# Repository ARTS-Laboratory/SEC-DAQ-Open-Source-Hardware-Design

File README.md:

# SEC DAQ
A 4-channel, 100 pF capacitance DAQ with active shielding designed for use with the Soft Elastomeric Capacitor (SEC) sensors but could be used for anything. 

This data acquisition can measure SECs in the range of 15-115 pF, with an asynchronous sampling speed of 400 S/s on a single channel.

This hardware was used in various papers, including:
1. Downey, Austin, Anna Laura Pisello, Elena Fortunati, Claudia Fabiani, Francesca Luzi, Luigi Torre, Filippo Ubertini, and Simon Laflamme. "Durability and weatherability of a styrene-ethylene-butylene-styrene (SEBS) block copolymer-based sensing skin for civil infrastructure applications." Sensors and Actuators A: Physical 293 (2019): 269-280.
1. Downey, Austin, Mohammadkazem Sadoughi, Simon Laflamme, and Chao Hu. "Fusion of sensor geometry into additive strain fields measured with sensing skin." Smart Materials and Structures 27, no. 7 (2018): 075033.
1. Yan, Jin, Austin Downey, Alessandro Cancelli, Simon Laflamme, An Chen, Jian Li, and Filippo Ubertini. "Concrete crack detection and monitoring using a capacitive dense sensor array." Sensors 19, no. 8 (2019): 1843.

## Hardware design notes

### v0.9.0
1. Contains all the older files. 
1. Contains the 2-board PCB design

### v0.9.1
1. This is stable release. 
1. A 4-channel SEC DAC with isolated signal

### v0.9.2 (future version)
Improvements needed

#### High importance
1. The files needs to be cleaned up, and put back into a single KiCad file.
1. Compress the board layout so the DAQ sits inside the Arduino shield. (Reduces the wasted space)
1. Remove the ground tabs as adding a shield is a further work outside of these single box DAQs
1. Use a lower current draw opotcoupler, I think a CPC1301 should work. 
 
#### Medium importance
1. Move trigger housing into the board so it does not hang over.
1. Change the surface mount D-sub to a edge mount D-sub with signal/shield on top and ground on bottom. 
1. Add a switch for the time stamp so the DAQ only returns a time stamp if the switch in enabled. Will require a 14 pin IDC connector.

#### Low importance 
1. Enlarge the CDC filter capacitor solder pads
1. Add LED to the trigger circuit to help with trouble shooting (check current draw problems)

## Licensing and Citation

[![CC BY-SA 4.0][cc-by-sa-shield]][cc-by-sa]

This work is licensed under a
[Creative Commons Attribution-ShareAlike 4.0 International License][cc-by-sa].

[cc-by-sa]: http://creativecommons.org/licenses/by-sa/4.0/
[cc-by-sa-image]: https://licensebuttons.net/l/by-sa/4.0/88x31.png
[cc-by-sa-shield]: https://img.shields.io/badge/License-CC%20BY--SA%204.0-lightgrey.svg

Cite as:

@Misc{DowneySECDAQ,   
  author       = {Austin Downey},   
  howpublished = {GitHub},  
  title        = {{SEC} {DAQ} Open Source Hardware Design},   
  groups       = {{ARTS-L}ab},  
  url          = {https://github.com/ARTS-Laboratory/SEC-DAQ-Open-Source-Hardware-Design},  
}

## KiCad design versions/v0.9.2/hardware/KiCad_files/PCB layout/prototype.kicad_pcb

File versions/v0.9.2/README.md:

# V0.9.2

## Hardware
PCB EDA files.

## Software
Arudino and LabVIEW source code.

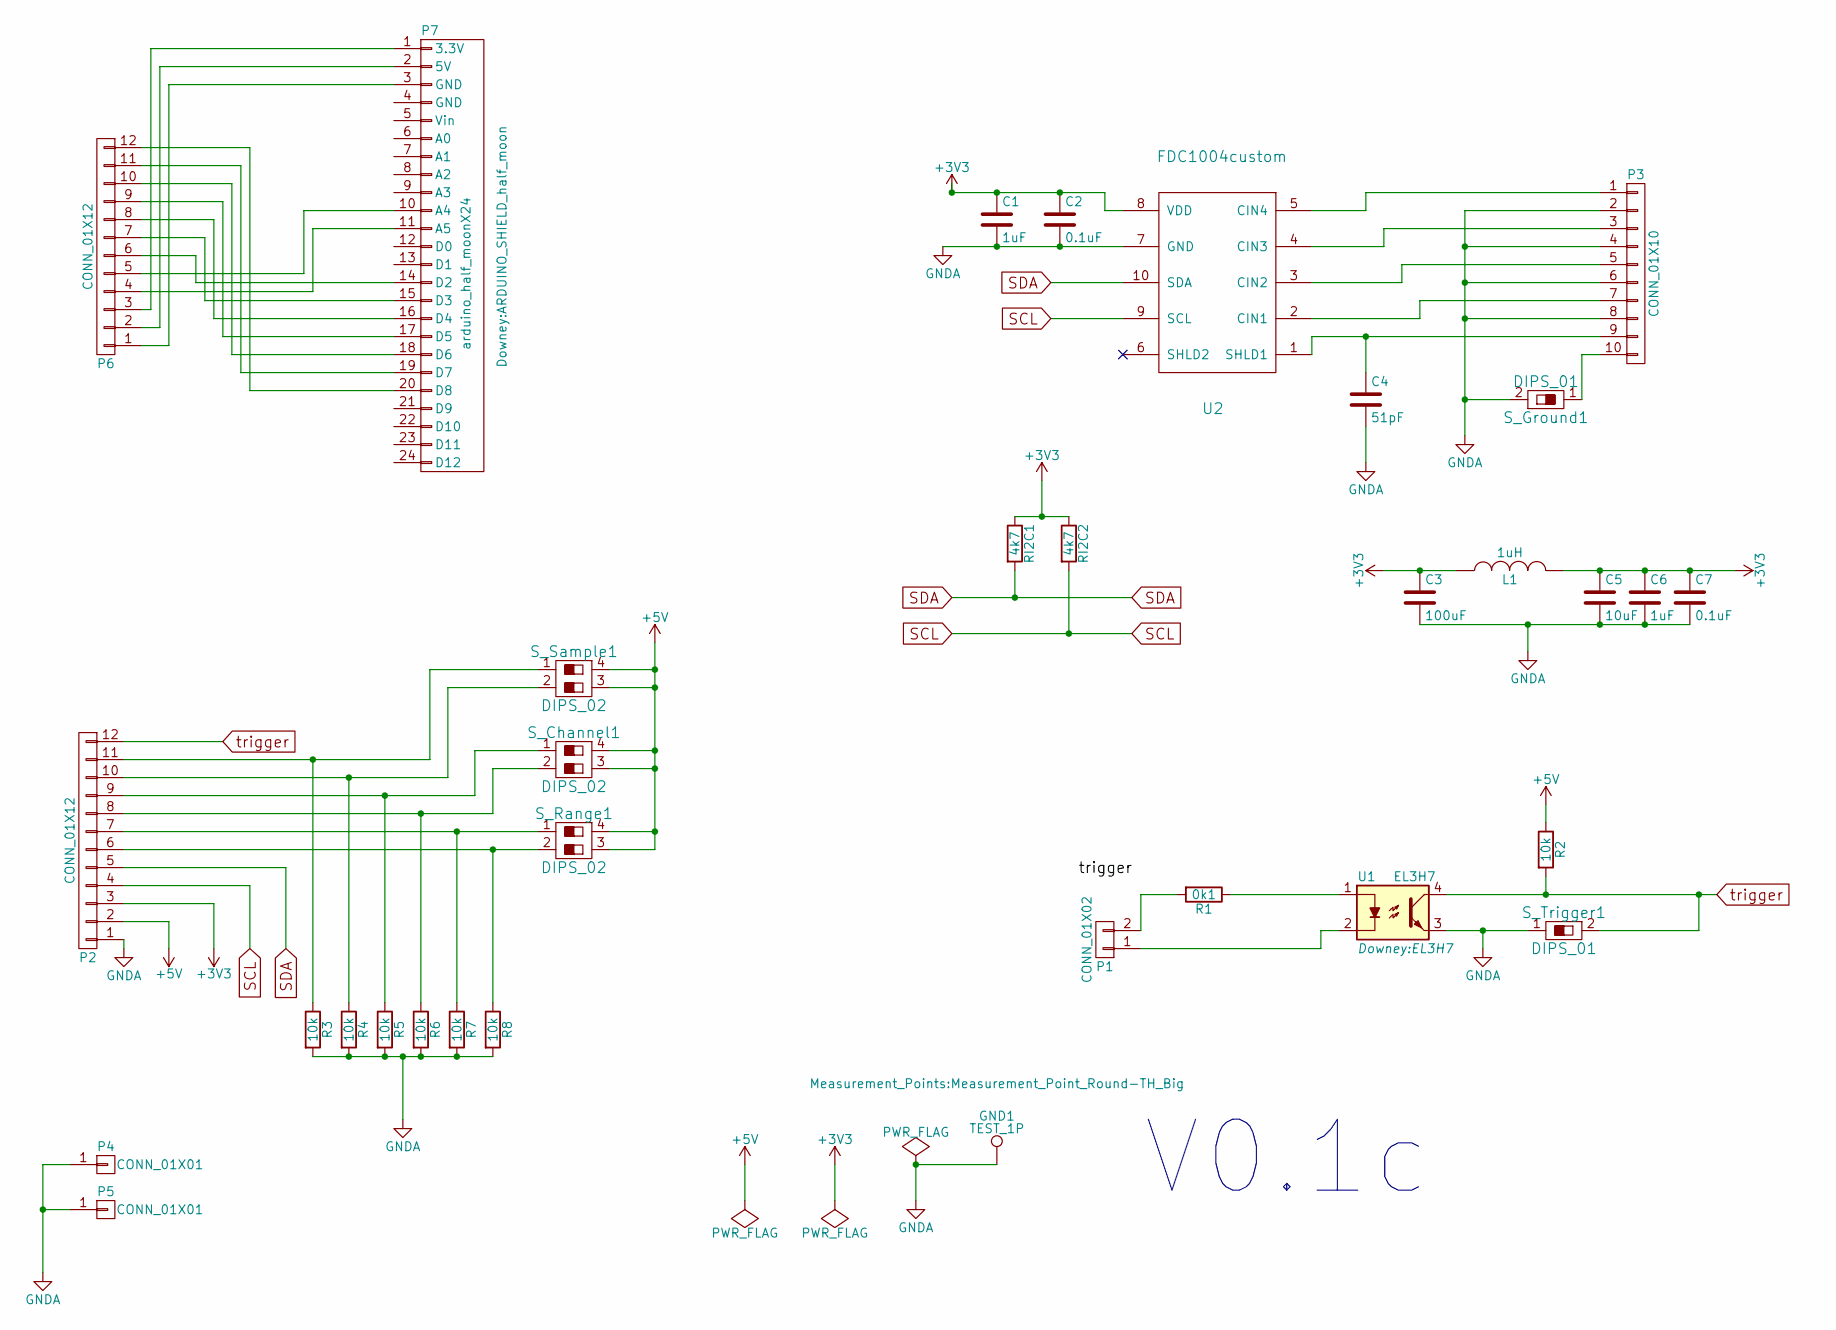
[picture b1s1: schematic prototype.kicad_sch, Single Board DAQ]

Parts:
C1, C6: 1uF; C_0805_HandSoldering
C2, C7: 0.1uF; C_0805_HandSoldering
C3: 100uF; C_1206_HandSoldering
C4: 51pF; C_0805_HandSoldering
C5: 10uF; C_0805_HandSoldering
GND1: TEST_1P; Measurement_Point_Round-TH_Big
L1: 1uH; R_0805_HandSoldering
P1: CONN_01X02; Pin_Header_Straight_1x02_Pitch2.00mm
P2, P6: CONN_01X12; 3M_12POS_ribbon_conn
P3: CONN_01X10; DSUB-9_surface_mount
P4, P5: CONN_01X01; 1Pin
P7: arduino_half_moonX24; ARDUINO_SHIELD_half_moon
R1: 0k1; R_1206_HandSoldering
R2, R3, R4, R5, R6, R7, R8: 10k; R_1206_HandSoldering
RI2C1, RI2C2: 4k7; R_1206_HandSoldering
S_Channel1: DIPS_02; SW_DIP_x2_W7.62mm_Slide
S_Ground1: DIPS_01; SW_DIP_x1_W7.62mm_Slide
S_Range1: DIPS_02; SW_DIP_x2_W7.62mm_Slide
S_Sample1: DIPS_02; SW_DIP_x2_W7.62mm_Slide
S_Trigger1: DIPS_01; SW_DIP_x1_W7.62mm_Slide
U1: EL3H7
U2: FDC1004custom; SOIC_10_FDC1004

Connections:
+3V3: C1.1, C2.1, C3.1, C5.1, C6.1, C7.1, L1.1, L1.2, P2.3, RI2C1.1, RI2C2.1, U2.8 (VDD)
+5V: P2.2, R2.1, S_Channel1.3, S_Channel1.4, S_Range1.3, S_Range1.4, S_Sample1.3, S_Sample1.4
GNDA: C1.2, C2.2, C3.2, C4.2, C5.2, C6.2, C7.2, GND1.1, P2.1, P3.2, P3.4, P3.6, P3.8, P4.1, P5.1, R3.2, R4.2, R5.2, R6.2, R7.2, R8.2, S_Ground1.2, S_Trigger1.1, U1.3, U2.7 (GND)
unnamed: C4.1, P3.9, U2.1 (SHLD1)
unnamed: P1.1, U1.2
unnamed: P1.2, R1.2
unnamed: P2.6, R8.1, S_Range1.2
unnamed: P2.7, R7.1, S_Range1.1
unnamed: P2.8, R6.1, S_Channel1.2
unnamed: P2.9, R5.1, S_Channel1.1
unnamed: P2.10, R4.1, S_Sample1.2
unnamed: P2.11, R3.1, S_Sample1.1
unnamed: P3.1, U2.5 (CIN4)
unnamed: P3.3, U2.4 (CIN3)
unnamed: P3.5, U2.3 (CIN2)
unnamed: P3.7, U2.2 (CIN1)
unnamed: P3.10, S_Ground1.1
unnamed: P6.1, P7.3 (GND)
unnamed: P6.2, P7.2 (5V)
unnamed: P6.3, P7.1 (3.3V)
unnamed: P6.4, P7.11 (A5)
unnamed: P6.5, P7.10 (A4)
unnamed: P6.6, P7.14 (D2)
unnamed: P6.7, P7.15 (D3)
unnamed: P6.8, P7.16 (D4)
unnamed: P6.9, P7.17 (D5)
unnamed: P6.10, P7.18 (D6)
unnamed: P6.11, P7.19 (D7)
unnamed: P6.12, P7.20 (D8)
unnamed: R1.1, U1.1
SCL: P2.4, RI2C2.2, U2.9 (SCL)
SDA: P2.5, RI2C1.2, U2.10 (SDA)
trigger: P2.12, R2.2, S_Trigger1.2, U1.4

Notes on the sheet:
V0.1c

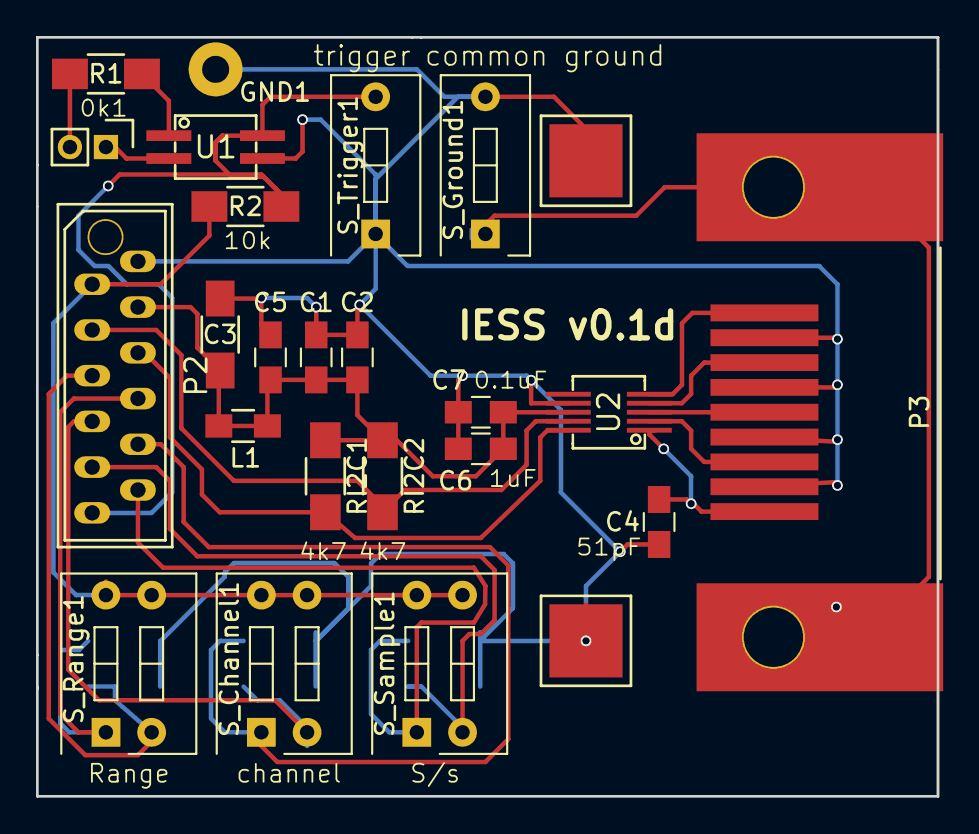
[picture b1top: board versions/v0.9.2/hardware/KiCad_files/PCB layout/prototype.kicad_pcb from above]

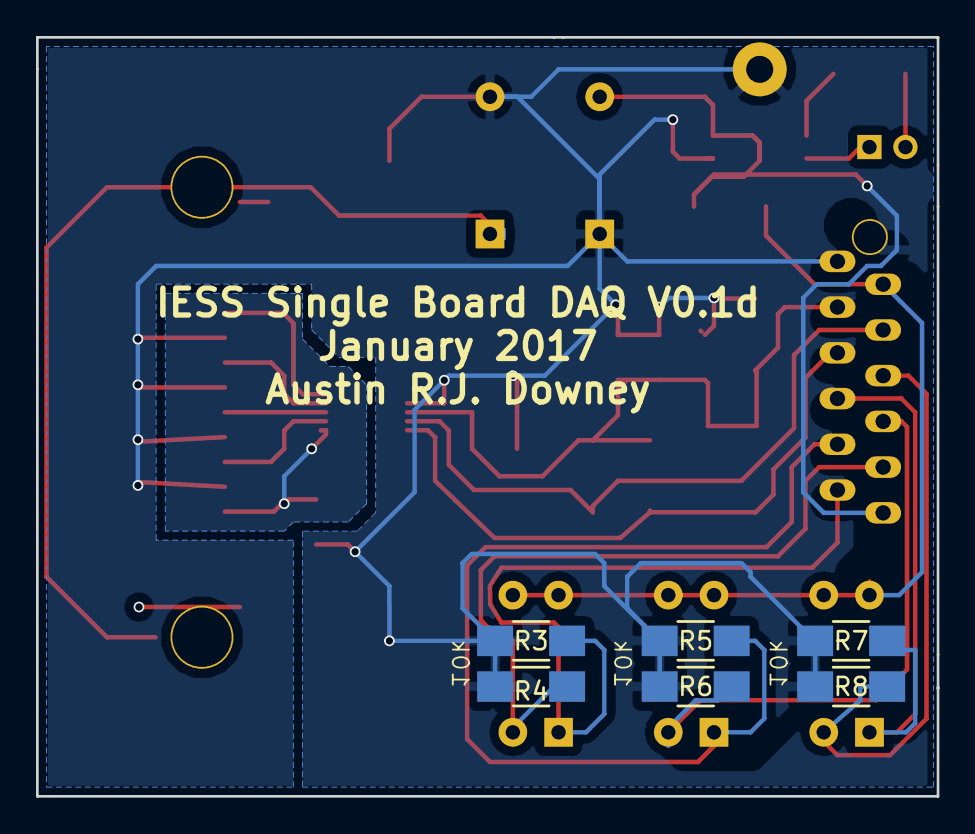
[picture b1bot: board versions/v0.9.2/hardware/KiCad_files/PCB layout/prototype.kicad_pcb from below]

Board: 2 copper layers, 50.0 x 42.2 mm, 31 parts (6 on the bottom side), 21 nets.

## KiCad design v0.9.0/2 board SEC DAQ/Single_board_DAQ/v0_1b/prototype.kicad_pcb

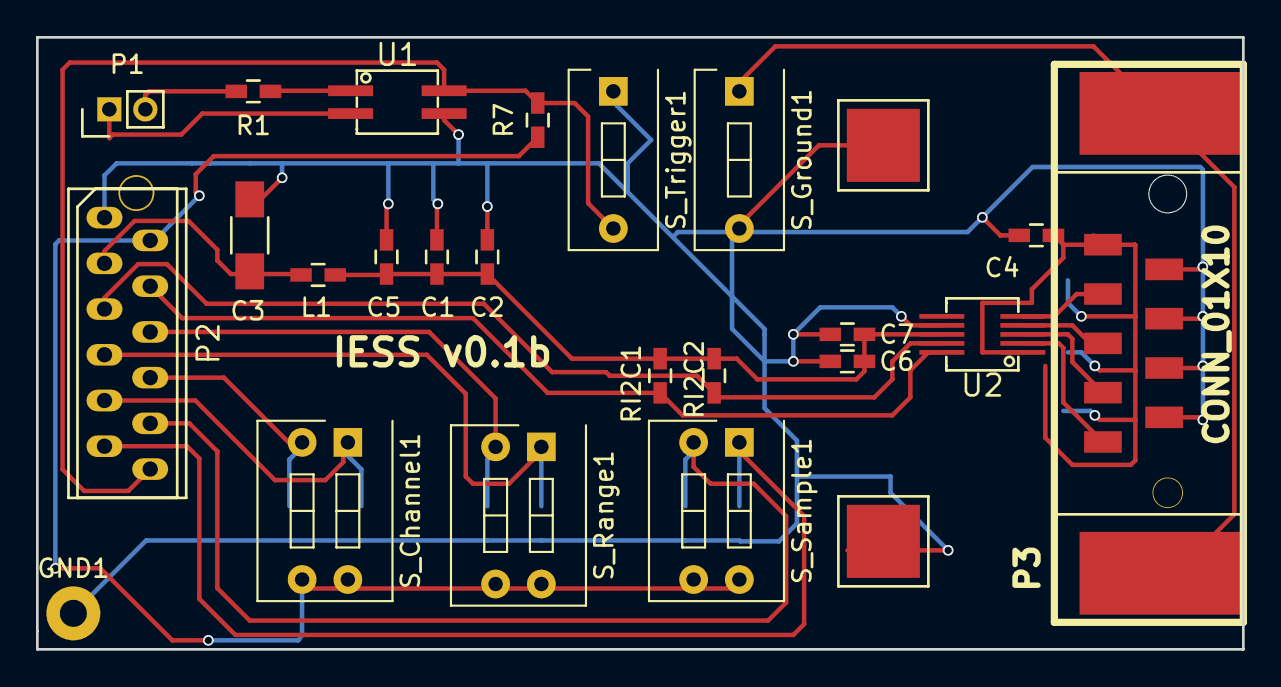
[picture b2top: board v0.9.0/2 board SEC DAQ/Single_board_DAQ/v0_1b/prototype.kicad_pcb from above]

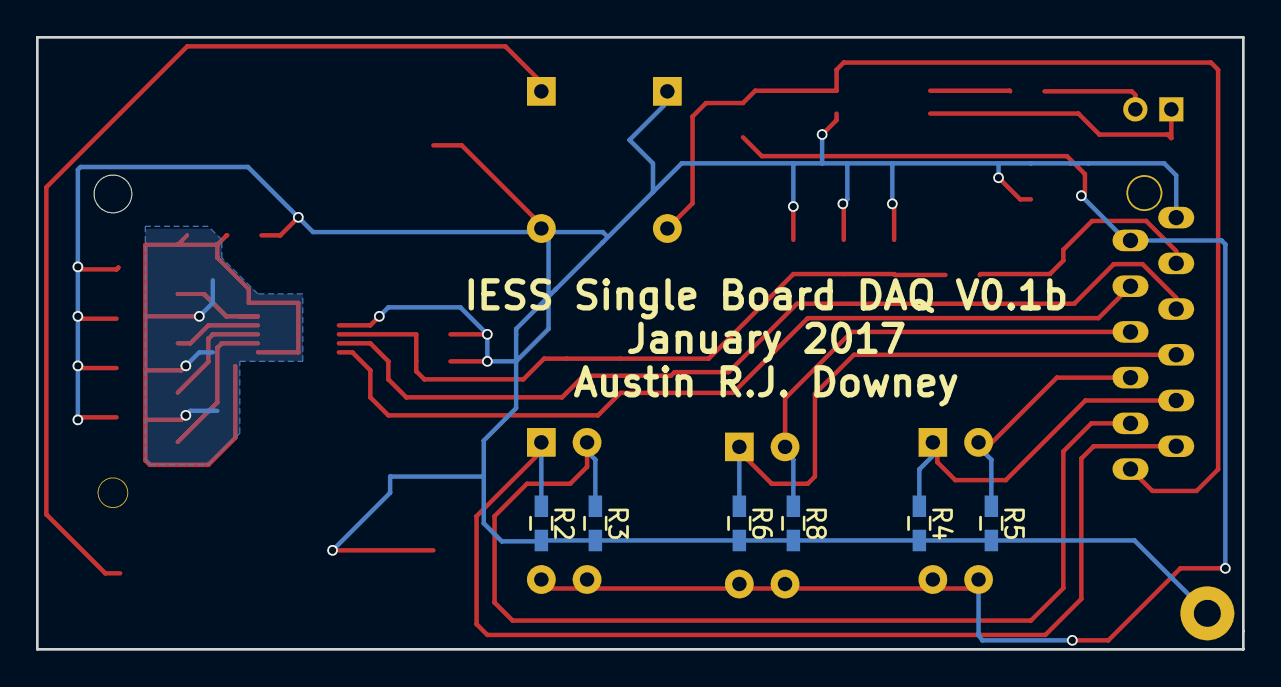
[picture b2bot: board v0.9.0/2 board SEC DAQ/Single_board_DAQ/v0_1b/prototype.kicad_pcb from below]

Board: 2 copper layers, 67.0 x 34.0 mm, 31 parts (6 on the bottom side), 21 nets.

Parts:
C1, C6: 1uF; C_0603_HandSoldering
C2, C7: 0.1uF; C_0603_HandSoldering
C3: 100uF; C_1206_HandSoldering
C4: 51pF; C_0603_HandSoldering
C5: 10uF; C_0603_HandSoldering
GND1: TEST_1P; Measurement_Point_Round-TH_Big
L1: 1uH; C_0603_HandSoldering
P1: CONN_01X02; Pin_Header_Straight_1x02_Pitch2.00mm
P2: CONN_01X12; 3M_12POS_ribbon_conn
P3: CONN_01X10; SMD_DSUB_9_female
P4, P5: CONN_01X01; 1Pin
R1: 0k1; C_0603_HandSoldering
R2, R3, R4, R5, R6, R7, R8: 10k; C_0603_HandSoldering
RI2C1, RI2C2: 4k7; C_0603_HandSoldering
S_Channel1: DIPS_02; SW_DIP_x2_W7.62mm_Slide
S_Ground1: DIPS_01; SW_DIP_x1_W7.62mm_Slide
S_Range1: DIPS_02; SW_DIP_x2_W7.62mm_Slide
S_Sample1: DIPS_02; SW_DIP_x2_W7.62mm_Slide
S_Trigger1: DIPS_01; SW_DIP_x1_W7.62mm_Slide
U1: EL3H7
U2: FDC1004custom; SOIC_10_FDC1004

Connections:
+3V3: C1.1, C2.1, C3.1, C5.1, C6.1, C7.1, L1.1, L1.2, P2.3, RI2C1.1, RI2C2.1, U2.8
+5V: P2.2, R7.1, S_Channel1.3, S_Channel1.4, S_Range1.3, S_Range1.4, S_Sample1.3, S_Sample1.4
GNDA: C1.2, C2.2, C3.2, C4.2, C5.2, C6.2, C7.2, GND1.1, P2.1, P3.2, P3.4, P3.6, P3.8, P4.1, P5.1, R2.2, R3.2, R4.2, R5.2, R6.2, R8.2, S_Ground1.2, S_Trigger1.1, U1.3, U2.7
unnamed: C4.1, P3.9, U2.1
unnamed: P1.1, U1.2
unnamed: P1.2, R1.2
unnamed: P2.6, R8.1, S_Range1.2
unnamed: P2.7, R6.1, S_Range1.1
unnamed: P2.8, R5.1, S_Channel1.2
unnamed: P2.9, R4.1, S_Channel1.1
unnamed: P2.10, R3.1, S_Sample1.2
unnamed: P2.11, R2.1, S_Sample1.1
unnamed: P3.1, U2.2
unnamed: P3.3, U2.3
unnamed: P3.5, U2.4
unnamed: P3.7, U2.5
unnamed: P3.10, S_Ground1.1
unnamed: R1.1, U1.1
SCL: P2.5, RI2C2.2, U2.9
SDA: P2.4, RI2C1.2, U2.10
trigger: P2.12, R7.2, S_Trigger1.2, U1.4

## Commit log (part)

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2021-01-29 initial upload
2021-10-20 cleaned up repo, added figure
2021-10-20 update image
2021-10-20 updated paper list
2021-11-15 licenses
